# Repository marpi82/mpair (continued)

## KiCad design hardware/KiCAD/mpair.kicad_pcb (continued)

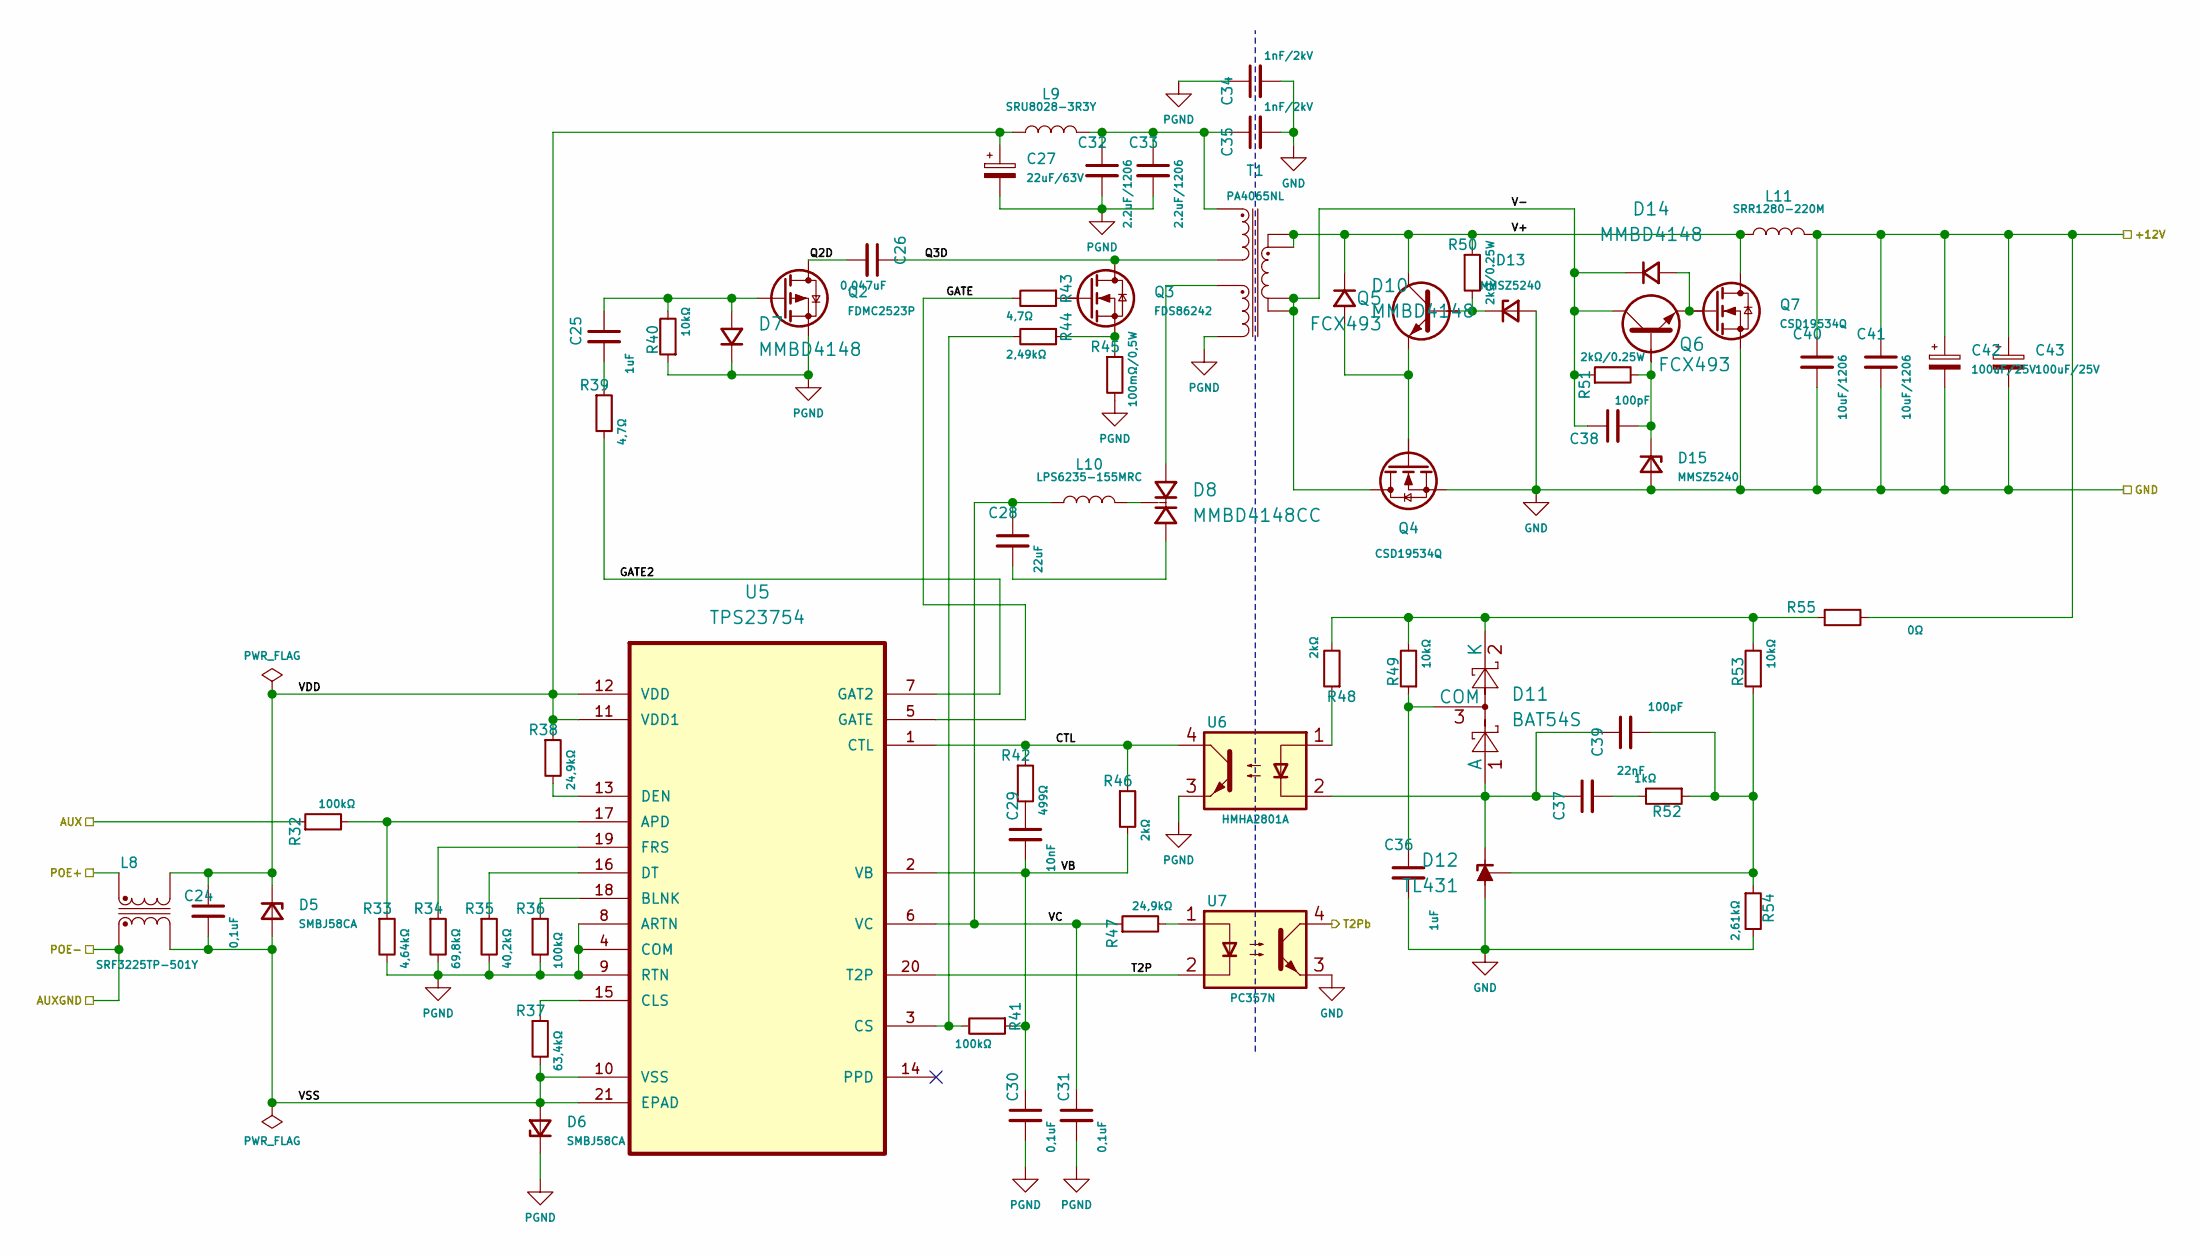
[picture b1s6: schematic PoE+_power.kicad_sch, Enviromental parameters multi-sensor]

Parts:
C24: 0,1uF; C_0805_2012Metric; Manufacturer_Part_Number Samsung; DigiKey_Part_Number 1276-6840-1-ND
C25, C36: 1uF; C_0805_2012Metric; Manufacturer_Part_Number Samsung; DigiKey_Part_Number 1276-1066-1-ND
C26: 0,047uF; C_1206_3216Metric; Manufacturer_Part_Number Kemet; DigiKey_Part_Number 399-C1206C473KARECTUCT-ND
C27: 22uF/63V; CP_Elec_8x6.2; Manufacturer_Part_Number Panasonic; DigiKey_Part_Number PCE3820CT-ND
C28: 22uF; C_1210_3225Metric; Manufacturer_Part_Number Samsung; DigiKey_Part_Number 1276-3392-1-ND
C29: 10nF; C_0603_1608Metric; Manufacturer_Part_Number Samsung; DigiKey_Part_Number 1276-1009-1-ND
C30, C31: 0,1uF; C_0603_1608Metric; Manufacturer_Part_Number Samsung; DigiKey_Part_Number 1276-1018-1-ND
C32, C33: 2.2uF/1206; C_1210_3225Metric; Manufacturer_Part_Number Samsung; DigiKey_Part_Number 1276-CL32B225KCJSNWECT-ND
C34, C35: 1nF/2kV; C_1812_4532Metric; Manufacturer_Part_Number Kemet; DigiKey_Part_Number 399-C1812C102KGRACTUCT-ND
C37: 22nF; C_0603_1608Metric; Manufacturer_Part_Number Murata; DigiKey_Part_Number 490-4782-1-ND
C38, C39: 100pF; C_0603_1608Metric; Manufacturer_Part_Number Samsung; DigiKey_Part_Number 1276-1008-1-ND
C40, C41: 10uF/1206; C_1210_3225Metric; Manufacturer_Part_Number TDK; DigiKey_Part_Number 445-3942-1-ND
C42, C43: 100uF/25V; CP_Elec_8x10; Manufacturer_Part_Number Panasonic; DigiKey_Part_Number PCE4003CT-ND
D5, D6: SMBJ58CA; D_SMB; Manufacturer_Part_Number Diodes Incorporated; DigiKey_Part_Number SMBJ58CA-FDICT-ND
D7, D10, D14: MMBD4148; SC-59; Manufacturer_Part_Number Taiwan Semiconductor Corporation; DigiKey_Part_Number 1801-MMBD4148RFGCT-ND
D8: MMBD4148CC; SC-59; Manufacturer_Part_Number Shenzhen Slkormicro Semicon Co., Ltd.; DigiKey_Part_Number 5399-MMBD4148CCCT-ND
D11: BAT54S; SC-59; Manufacturer_Part_Number Shenzhen Slkormicro Semicon Co., Ltd.; DigiKey_Part_Number 5399-BAT54SCT-ND
D12: TL431; SC-59; Tolerance 5%; Manufacturer_Part_Number Texas Instruments; DigiKey_Part_Number 296-17329-1-ND
D13, D15: MMSZ5240; D_SOD-123; Manufacturer_Part_Number Shenzhen Slkormicro Semicon Co., Ltd.; DigiKey_Part_Number 5399-MMSZ5240BCT-ND
L8: SRF3225TP-501Y; SRF3225TAC_BRN; Manufacturer_Part_Number Bourns Inc.; DigiKey_Part_Number 118-SRF3225TP-501YCT-ND
L9: SRU8028-3R3Y; L_Bourns-SRU8028_8.0x8.0mm; Manufacturer_Part_Number Bourns Inc.; DigiKey_Part_Number SRU8028-3R3YCT-ND
L10: LPS6235-155MRC; L_TDK_SLF10145; Manufacturer_Part_Number TDK Corporation; DigiKey_Part_Number 445-1980-1-ND
L11: SRR1280-220M; L_Bourns_SRR1280; Manufacturer_Part_Number Bourns Inc.; DigiKey_Part_Number SRR1280-220MCT-ND
Q2: FDMC2523P; FDMC_2523P; Manufacturer_Part_Number onsemi; DigiKey_Part_Number FDMC2523PCT-ND
Q3: FDS86242; FDS_86242; Manufacturer_Part_Number onsemi; DigiKey_Part_Number FDS86242CT-ND
Q4, Q7: CSD19534Q; Manufacturer_Part_Number Texas Instruments; DigiKey_Part_Number 296-37838-1-ND
Q5, Q6: FCX493; SOT-89-3; Manufacturer_Part_Number Diodes Incorporated; DigiKey_Part_Number 31-FCX493QTACT-ND
R32, R36, R41: 100kΩ; R_0603_1608Metric; Tolerance 1%; Manufacturer_Part_Number Vishay Dale; DigiKey_Part_Number 541-100KHCT-ND
R33: 4,64kΩ; R_0603_1608Metric; Tolerance 1%; Manufacturer_Part_Number Vishay Dale; DigiKey_Part_Number 541-4.64KHCT-ND
R34: 69,8kΩ; R_0603_1608Metric; Tolerance 1%; Manufacturer_Part_Number Vishay Dale; DigiKey_Part_Number 541-69.8KHCT-ND
R35: 40,2kΩ; R_0603_1608Metric; Tolerance 1%; Manufacturer_Part_Number Vishay Dale; DigiKey_Part_Number 541-40.2KHCT-ND
R37: 63,4kΩ; R_0603_1608Metric; Tolerance 1%; Manufacturer_Part_Number Vishay Dale; DigiKey_Part_Number 541-63.4KHCT-ND
R38, R47: 24,9kΩ; R_0603_1608Metric; Tolerance 1%; Manufacturer_Part_Number Vishay Dale; DigiKey_Part_Number 541-24.9KHCT-ND
R39, R43: 4,7Ω; R_0603_1608Metric; Tolerance 1%; Manufacturer_Part_Number Vishay Dale; DigiKey_Part_Number 541-4.70HHCT-ND
R40, R49, R53: 10kΩ; R_0603_1608Metric; Tolerance 1%; Manufacturer_Part_Number Vishay Dale; DigiKey_Part_Number 541-10.0KHCT-ND
R42: 499Ω; R_0603_1608Metric; Tolerance 1%; Manufacturer_Part_Number Vishay Dale; DigiKey_Part_Number 541-499HCT-ND
R44: 2,49kΩ; R_0603_1608Metric; Tolerance 1%; Manufacturer_Part_Number Vishay Dale; DigiKey_Part_Number 541-2.49KHCT-ND
R45: 100mΩ/0,5W; R_1206_3216Metric; Tolerance 1%; Manufacturer_Part_Number Vishay Dale; DigiKey_Part_Number 541-2740-1-ND
R46, R48: 2kΩ; R_0603_1608Metric; Tolerance 1%; Manufacturer_Part_Number Vishay Dale; DigiKey_Part_Number 541-2.00KHCT-ND
R50, R51: 2kΩ/0.25W; R_0805_2012Metric; Tolerance 1%; Manufacturer_Part_Number Vishay Dale; DigiKey_Part_Number 541-2.00KCCT-ND
R52: 1kΩ; R_0603_1608Metric; Tolerance 1%; Manufacturer_Part_Number Vishay Dale; DigiKey_Part_Number 541-1.00KHCT-ND
R54: 2,61kΩ; R_0603_1608Metric; Tolerance 1%; Manufacturer_Part_Number Vishay Dale; DigiKey_Part_Number 541-2.61KHCT-ND
R55: 0Ω; R_0603_1608Metric; Tolerance 1%; Manufacturer_Part_Number Vishay Dale; DigiKey_Part_Number 541-0.0GCT-ND
T1: PA4065NL; Manufacturer_Part_Number PA4065NL; Mouser Part Number N/A
U5: TPS23754; HTSSOP-20-1EP_4.4x6.5mm_P0.65mm_EP2.85x4mm; MPN TPS23754PWPR; DigiKey_Part_Number 296-39367-1-ND
U6: HMHA2801A; SOIC-4_4.55x2.6mm_P1.27mm; Manufacturer_Part_Number onsemi; DigiKey_Part_Number HMHA2801AR2VCT-ND
U7: PC357N; OnSemi_751EP_SOIC-4_3.9x4.725mm_P2.54mm; Manufacturer_Part_Number SHARP/Socle Technology; DigiKey_Part_Number 1855-1022-1-ND

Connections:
+12V: C40.1, C41.1, C42.1, C43.1, L11.2, R55.2; also elsewhere on the board
/ESP32-C6/T2Pb: U7.4; also elsewhere on the board
/PoE+ power supply/AUX: R32.1; also elsewhere on the board
/PoE+ power supply/AUXGND: L8.4; also elsewhere on the board
/PoE+ power supply/CTL: R42.1, R46.1, U5.1 (CTL), U6.4
/PoE+ power supply/GATE: R43.2, U5.5 (GATE)
/PoE+ power supply/GATE2: R39.2, U5.7 (GAT2)
/PoE+ power supply/POE+: L8.1; also elsewhere on the board
/PoE+ power supply/Q2D: C26.2, Q2.D
/PoE+ power supply/Q3D: C26.1, Q3.D, T1.2
/PoE+ power supply/T2P: U5.20 (T2P), U7.2
/PoE+ power supply/V+: D10.3 (K), L11.1, Q5.2 (C), Q7.D, R50.1, T1.6, T1.7
/PoE+ power supply/V-: C38.1, D14.3 (K), Q4.D, Q6.2 (C), R51.1, T1.9, T1.10
/PoE+ power supply/VB: C29.2, C30.1, R41.1, R46.2, U5.2 (VB)
/PoE+ power supply/VC: C28.1, C31.1, L10.1, R47.1, U5.6 (VC)
/PoE+ power supply/VDD: C24.1, C27.1, D5.1 (K), L8.2, L9.1, R38.1, U5.11 (VDD1), U5.12 (VDD)
/PoE+ power supply/VSS: C24.2, D5.2 (A), D6.2 (A), L8.3, R37.2, U5.10 (VSS), U5.21 (EPAD)
GND: C34.2, C35.2, C36.2, C40.2, C41.2, C42.2, C43.2, D12.3 (A), D13.2 (A), D15.2 (A), Q4.S, Q7.S, R54.2, U7.3; also elsewhere on the board
unnamed: C25.2, R39.1
unnamed: C29.1, R42.2
unnamed: C32.1, C33.1, C35.1, L9.2, T1.1
unnamed: C37.2, R52.2
unnamed: C25.1, D7.1 (A), Q2.G, R40.2
unnamed: D8.1 (A1), T1.4
unnamed: C28.2, D8.2 (A2)
unnamed: D8.3 (K), L10.2
unnamed: D10.1 (A), Q4.G, Q5.3 (E)
unnamed: C37.1, C39.1, D11.1 (A), D12.1 (K), U6.2
unnamed: C36.1, D11.3 (COM), R49.1
unnamed: D11.2 (K), R48.2, R49.2, R53.2, R55.1
unnamed: C39.2, D12.2 (REF), R52.1, R53.1, R54.1
unnamed: D13.1 (K), Q5.1 (B), R50.2
unnamed: D14.1 (A), Q6.3 (E), Q7.G
unnamed: C38.2, D15.1 (K), Q6.1 (B), R51.2
unnamed: Q3.G, R43.1
unnamed: Q3.S, R44.1, R45.1
unnamed: R47.2, U7.1
unnamed: R48.1, U6.1
unnamed: R32.2, R33.1, U5.17 (APD)
unnamed: R36.1, U5.18 (BLNK)
unnamed: R37.1, U5.15 (CLS)
unnamed: R41.2, R44.2, U5.3 (CS)
unnamed: R38.2, U5.13 (DEN)
unnamed: R35.1, U5.16 (DT)
unnamed: R34.1, U5.19 (FRS)
PGND: C27.2, C30.2, C31.2, C32.2, C33.2, C34.1, D6.1 (K), D7.3 (K), Q2.S, R33.2, R34.2, R35.2, R36.2, R40.1, R45.2, T1.5, U5.4 (COM), U5.8 (ARTN), U5.9 (RTN), U6.3

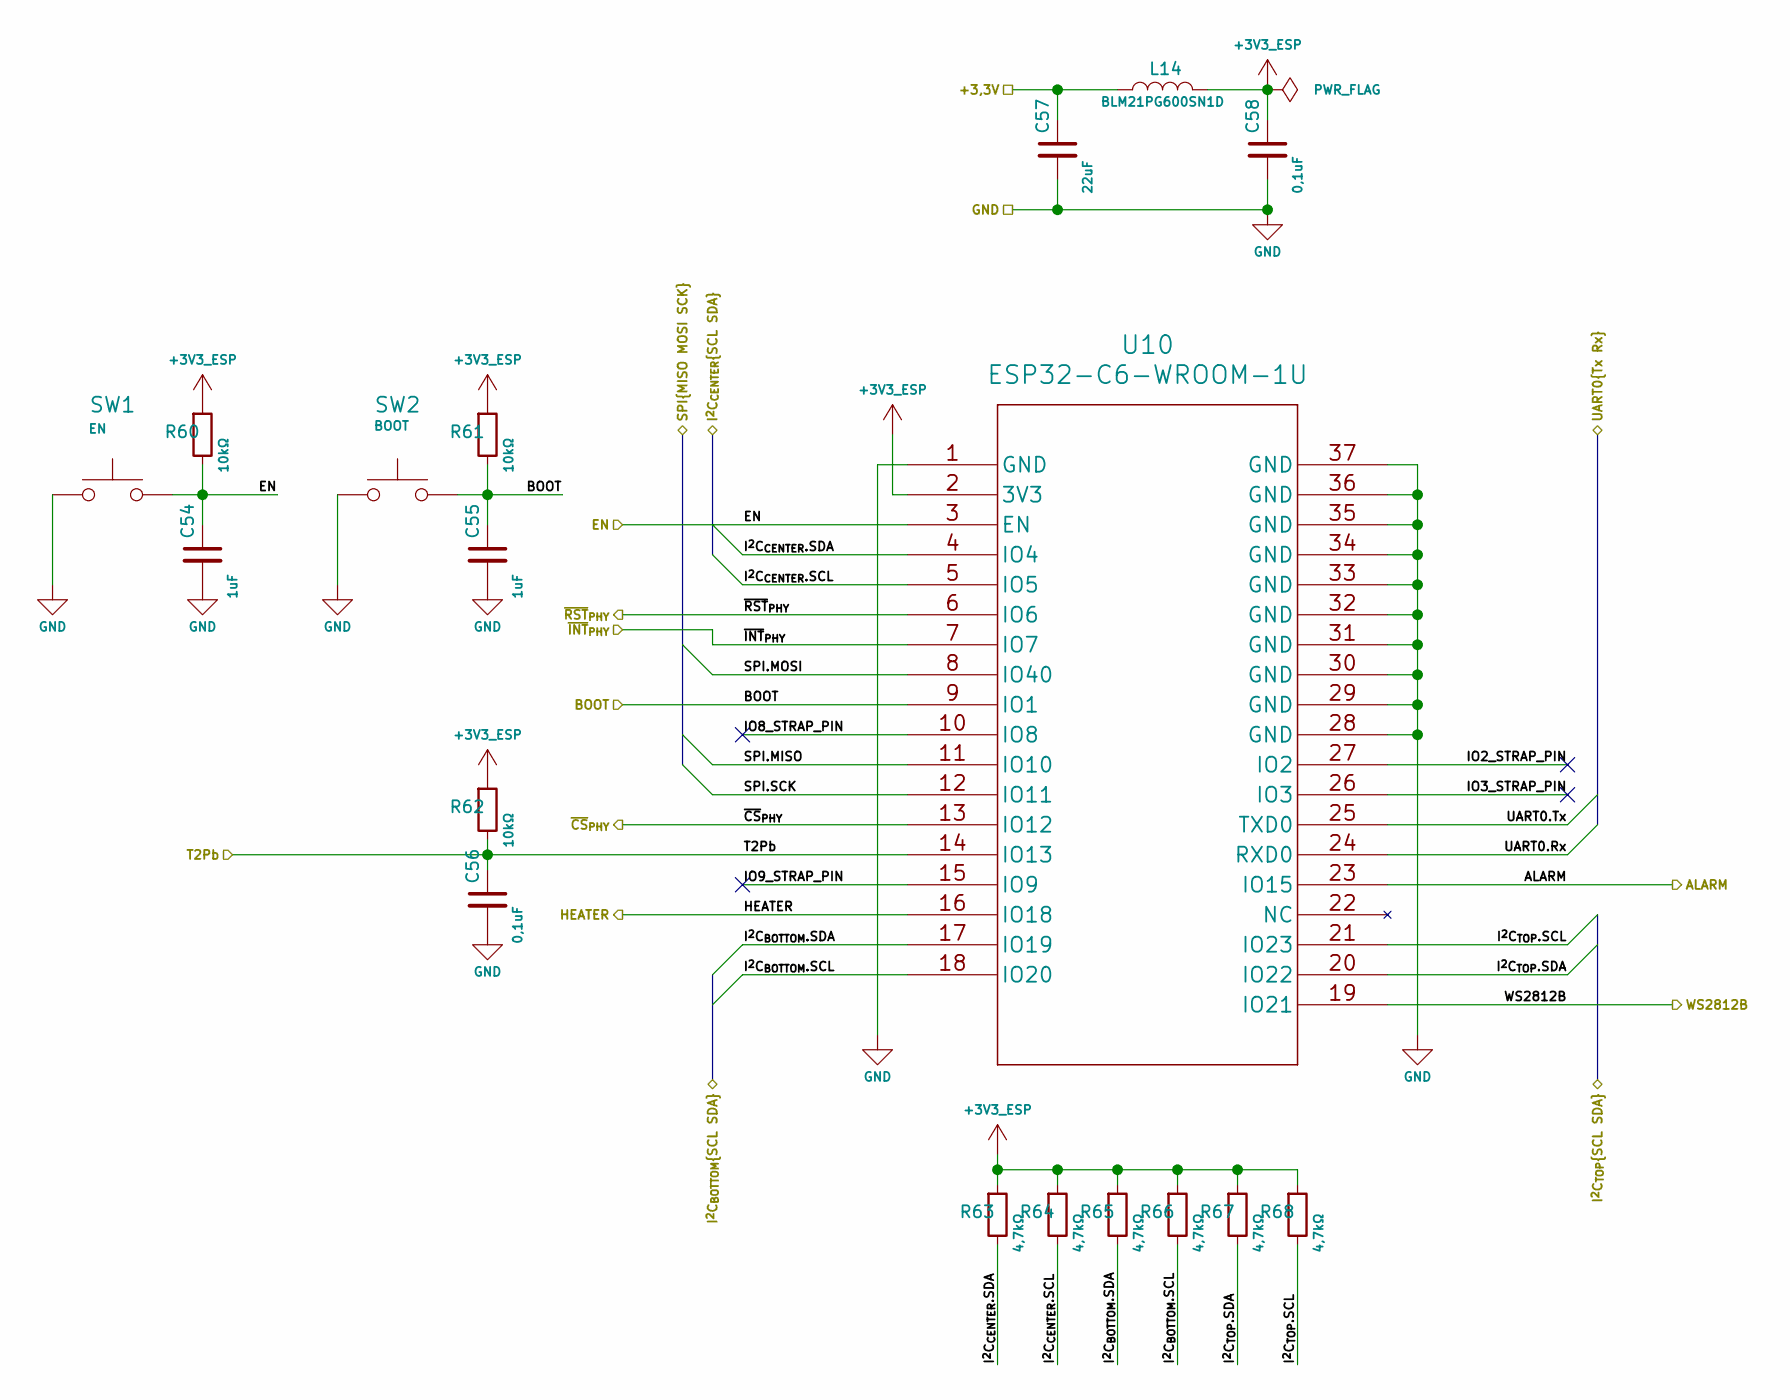
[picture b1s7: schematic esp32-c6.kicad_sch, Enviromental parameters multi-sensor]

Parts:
C54, C55: 1uF; C_0805_2012Metric; Manufacturer_Part_Number Samsung; DigiKey_Part_Number 1276-1066-1-ND
C56, C58: 0,1uF; C_0603_1608Metric; Manufacturer_Part_Number Samsung; DigiKey_Part_Number 1276-1018-1-ND
C57: 22uF; C_1210_3225Metric; Manufacturer_Part_Number Samsung; DigiKey_Part_Number 1276-3392-1-ND
L14: BLM21PG600SN1D; L_0805_2012Metric; Manufacturer_Part_Number Murata Electronics; DigiKey_Part_Number 490-1053-1-ND
R60, R61, R62: 10kΩ; R_0603_1608Metric; Tolerance 1%; Manufacturer_Part_Number Vishay Dale; DigiKey_Part_Number 541-10.0KHCT-ND
R63, R64, R65, R66, R67, R68: 4,7kΩ; R_0603_1608Metric; Tolerance 1%; Manufacturer_Part_Number Vishay Dale; DigiKey_Part_Number 541-4.70KHCT-ND
SW1, SW2: SW_SPST_FSMSM; Manufacturer_Part_Number TE Connectivity; DigiKey_Part_Number 450-1140-ND
U10: ESP32-C6-WROOM-1U; Manufacturer_Part_Number Espressif Systems; DigiKey_Part_Number 1965-ESP32-C6-WROOM-1U-N8CT-ND

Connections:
+3.3V: C57.1, L14.1; also elsewhere on the board
+3V3_ESP: C58.1, L14.2, R60.1, R61.1, R62.1, R63.1, R64.1, R65.1, R66.1, R67.1, R68.1, U10.2 (3V3)
/ESP32-C6/ALARM: U10.23 (IO15); also elsewhere on the board
/ESP32-C6/BOOT: C55.1, R61.2, SW2.2, U10.9 (IO1); also elsewhere on the board
/ESP32-C6/EN: C54.1, R60.2, SW1.2, U10.3 (EN); also elsewhere on the board
/ESP32-C6/HEATER: U10.16 (IO18); also elsewhere on the board
/ESP32-C6/IO2_STRAP_PIN: U10.27 (IO2)
/ESP32-C6/IO3_STRAP_PIN: U10.26 (IO3)
/ESP32-C6/IO8_STRAP_PIN: U10.10 (IO8)
/ESP32-C6/IO9_STRAP_PIN: U10.15 (IO9)
/ESP32-C6/I^{2}C_{BOTTOM}.SCL: R66.2, U10.18 (IO20); also elsewhere on the board
/ESP32-C6/I^{2}C_{BOTTOM}.SDA: R65.2, U10.17 (IO19); also elsewhere on the board
/ESP32-C6/I^{2}C_{CENTER}.SCL: R64.2, U10.5 (IO5); also elsewhere on the board
/ESP32-C6/I^{2}C_{CENTER}.SDA: R63.2, U10.4 (IO4); also elsewhere on the board
/ESP32-C6/I^{2}C_{TOP}.SCL: R68.2, U10.21 (IO23); also elsewhere on the board
/ESP32-C6/I^{2}C_{TOP}.SDA: R67.2, U10.20 (IO22); also elsewhere on the board
/ESP32-C6/SPI.MISO: U10.11 (IO10); also elsewhere on the board
/ESP32-C6/SPI.MOSI: U10.8 (IO40); also elsewhere on the board
/ESP32-C6/SPI.SCK: U10.12 (IO11); also elsewhere on the board
/ESP32-C6/T2Pb: C56.1, R62.2, U10.14 (IO13); also elsewhere on the board
/ESP32-C6/UART0.Rx: U10.24 (RXD0); also elsewhere on the board
/ESP32-C6/UART0.Tx: U10.25 (TXD0); also elsewhere on the board
/ESP32-C6/WS2812B: U10.19 (IO21); also elsewhere on the board
/ESP32-C6/~CS_{PHY}: U10.13 (IO12); also elsewhere on the board
/ESP32-C6/~INT_{PHY}: U10.7 (IO7); also elsewhere on the board
/ESP32-C6/~RST_{PHY}: U10.6 (IO6); also elsewhere on the board
GND: C54.2, C55.2, C56.2, C57.2, C58.2, SW1.1, SW2.1, U10.1 (GND), U10.28 (GND), U10.29 (GND), U10.30 (GND), U10.31 (GND), U10.32 (GND), U10.33 (GND), U10.34 (GND), U10.35 (GND), U10.36 (GND), U10.37 (GND); also elsewhere on the board

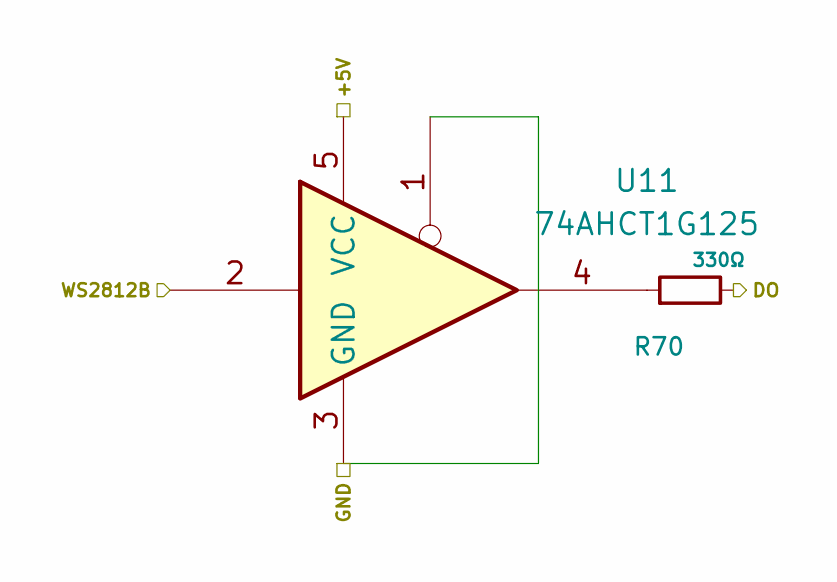
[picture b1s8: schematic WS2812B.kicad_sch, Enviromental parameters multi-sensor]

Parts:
R70: 330Ω; R_0603_1608Metric; Tolerance 1%; Manufacturer_Part_Number Vishay Dale; DigiKey_Part_Number 541-330HCT-ND
U11: 74AHCT1G125; SOT-353_SC-70-5; Manufacturer_Part_Number Texas Instruments; DigiKey_Part_Number 296-4709-1-ND

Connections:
+5V: U11.5 (VCC); also elsewhere on the board
/ESP32-C6/WS2812B: U11.2; also elsewhere on the board
/WS2812B/DO: R70.2; also elsewhere on the board
GND: U11.1, U11.3 (GND); also elsewhere on the board
unnamed: R70.1, U11.4

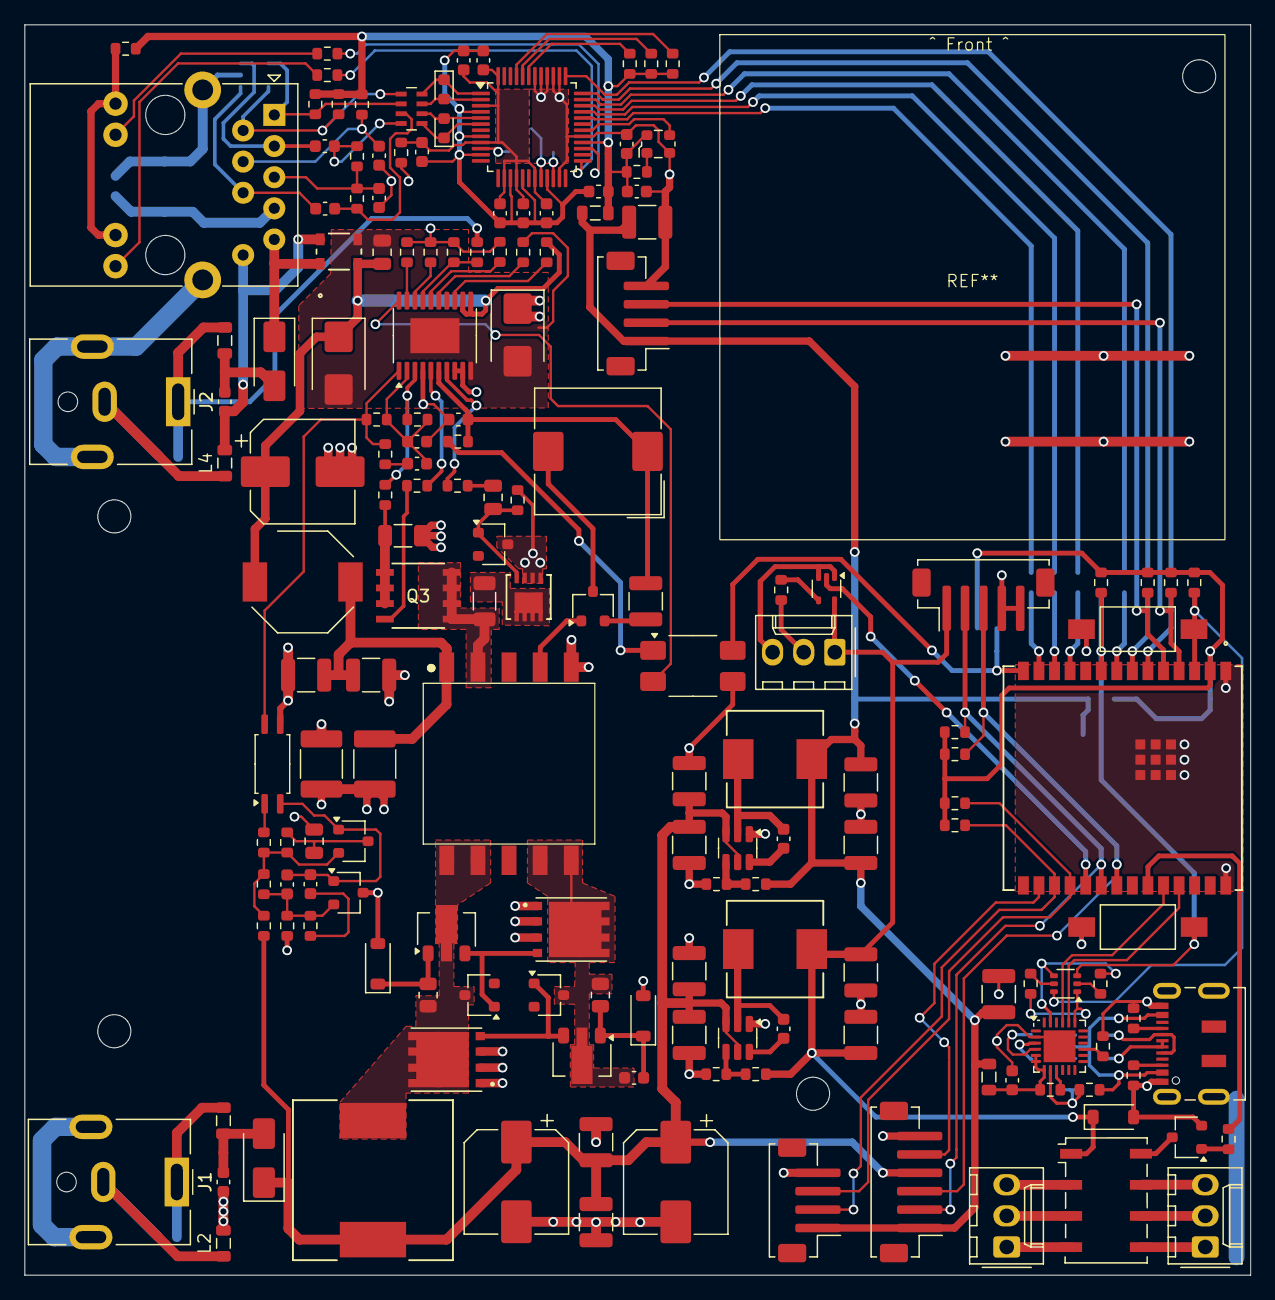
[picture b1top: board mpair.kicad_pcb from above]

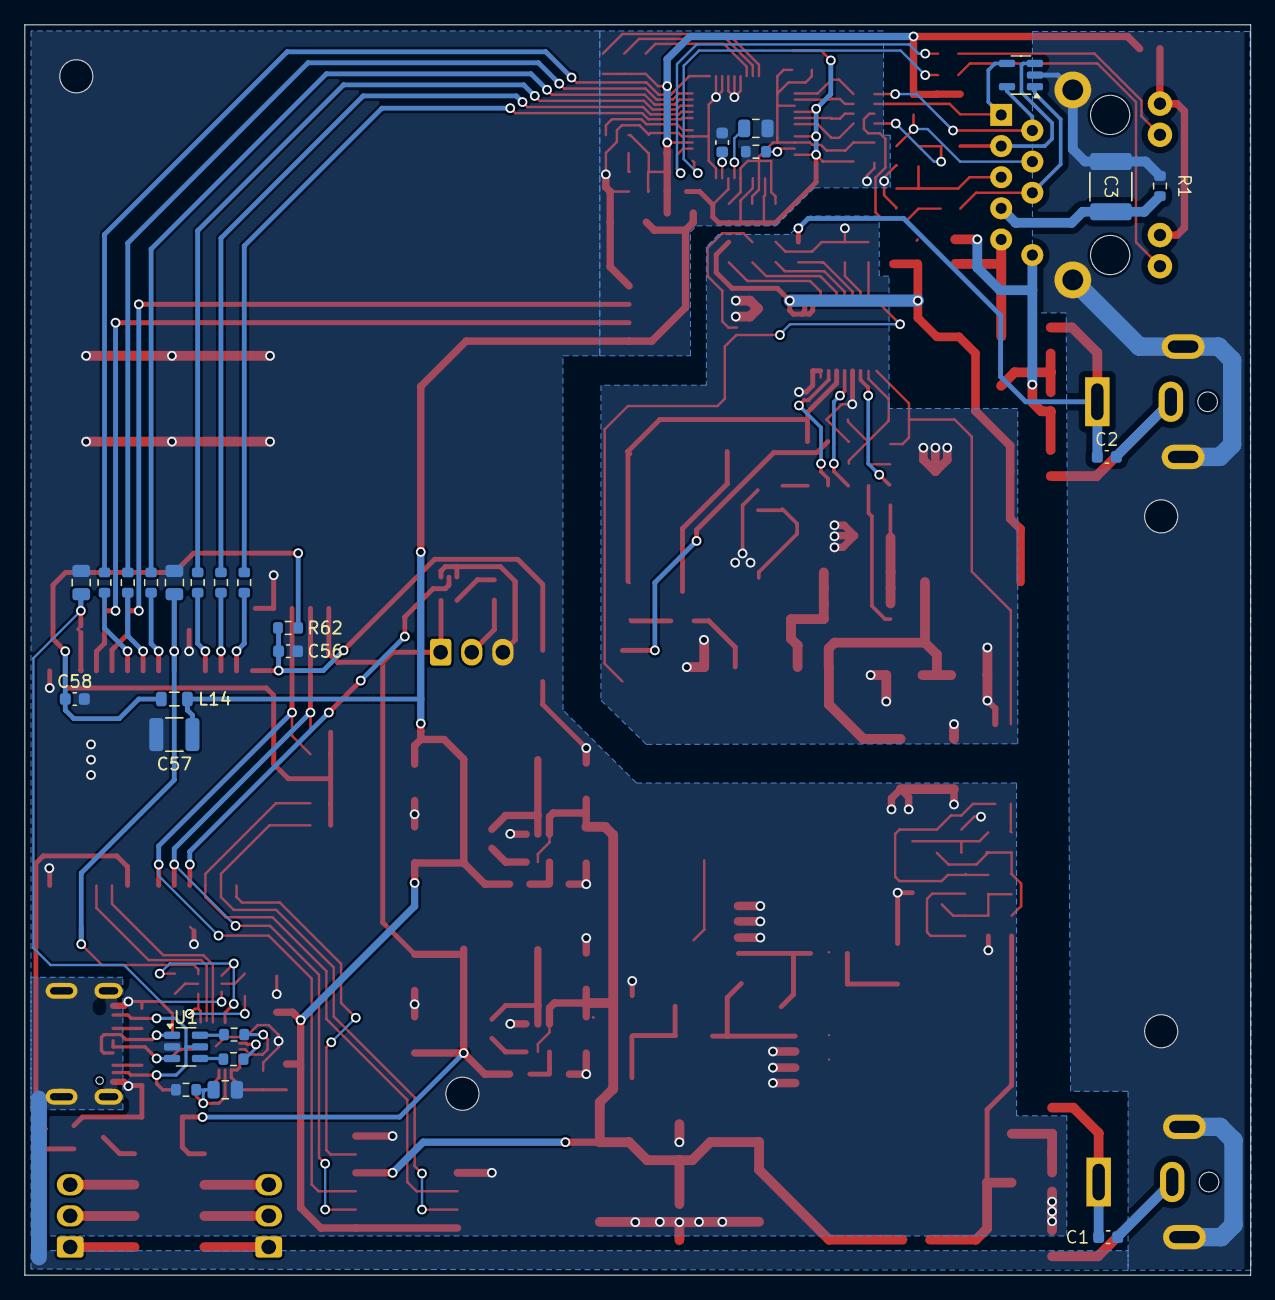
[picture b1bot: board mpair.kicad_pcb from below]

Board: 2 copper layers, 100.0 x 102.0 mm, 197 parts (26 on the bottom side), 142 nets.

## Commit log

2026-01-03 docs: Add project README and license files in Polish and English
    - Add README.rst (English) and README.pl.rst (Polish) with full project documentation
    - Add LICENSE-hardware.rst/pl.rst (CERN-OHL-S-2.0)
    - Add LICENSE-software.rst/pl.rst (GPL-3.0)
    - Add LICENSE-docs.rst/pl.rst (CC BY-SA 4.0)
    - Include technical specifications, features, and getting started guide
    - Add multiple data export protocols (MQTT, Prometheus, Luftdaten, etc.)
2026-01-03 feat: Add complete ESP-IDF development environment
    - Add firmware-s3 (ESP32-S3 main controller)
    * CMake configuration with ESP-IDF v5.3
    * Basic main.c with initialization
    * sdkconfig.defaults with Ethernet, USB-CDC, PSRAM
    * Partition table for OTA updates
    * README with setup instructions
2026-01-03 docs: Update ESP-IDF version to v5.5.2
    - Update all references from v5.3/v5.1 to v5.5.2
    - Update installation guide
    - Update VS Code settings and Python env path
    - Update README files for both firmwares
    - Add version requirements to CMakeLists.txt
2026-01-03 ci: Add comprehensive CI/CD pipeline and pre-commit hooks
    GitHub Actions Workflows:
    - build.yml: Automated firmware compilation for ESP32-S3 and ESP32-H2
    * Uses espressif/idf:v5.5.2 Docker image
    * Uploads build artifacts for 30 days
    * Parallel builds with summary report
    - code-quality.yml: Code quality checks
2026-01-03 scripts: Add automated development tools setup
    Add scripts for easy local development environment setup:
    - setup-tools.sh: Automated installation script
    * Detects OS (Linux/macOS) and installs appropriate packages
    * Installs system tools (clang-format, cmake, ninja)
    * Installs Node.js and markdownlint-cli
    * Creates Python virtual environment (.venv-tools/)
2026-01-03 feat: add AI agent instructions and update development tools
    - Add .github/copilot-instructions.md for AI coding agents
    - Update pre-commit hooks to v6.0.0+ (latest versions)
    - Fix clang-format compatibility (use generic package instead of v14)
    - Update black to 25.12.0 with python3 (removed python3.11 requirement)
    - Add .secrets.baseline for detect-secrets
    - Fix all Markdown formatting issues (MD060 table styles, MD040 code blocks)
2026-01-04 update power supply
2026-01-04 W5500 wiring
2026-01-04 W5500 PMODE switch wiring
2026-01-05 Update USB/UART/ESP32-C6
2026-01-07 added Altium project (not completed)
2026-01-07 Refactor: Migrate from dual MCU (ESP32-S3+H2) to single ESP32-C6 with W5500 Ethernet
    Major architecture changes:
    - Replace ESP32-S3 + ESP32-H2 dual MCU with single ESP32-C6
    - Native 802.15.4 radio for Matter/Thread (no separate gateway MCU)
    - W5500 SPI Ethernet controller instead of RMII PHY (LAN8710A)
    - CP2102 USB-UART converter for programming (instead of direct USB)
    - WiFi 6 (802.11ax) 2.4GHz support
2026-01-16 update ESP32
2026-01-22 added new KiCAD hardware design
2026-01-24 Stop tracking Altium/EasyEDA projects
2026-01-27 added data publisher aqi.eco
2026-02-02 update PCB
